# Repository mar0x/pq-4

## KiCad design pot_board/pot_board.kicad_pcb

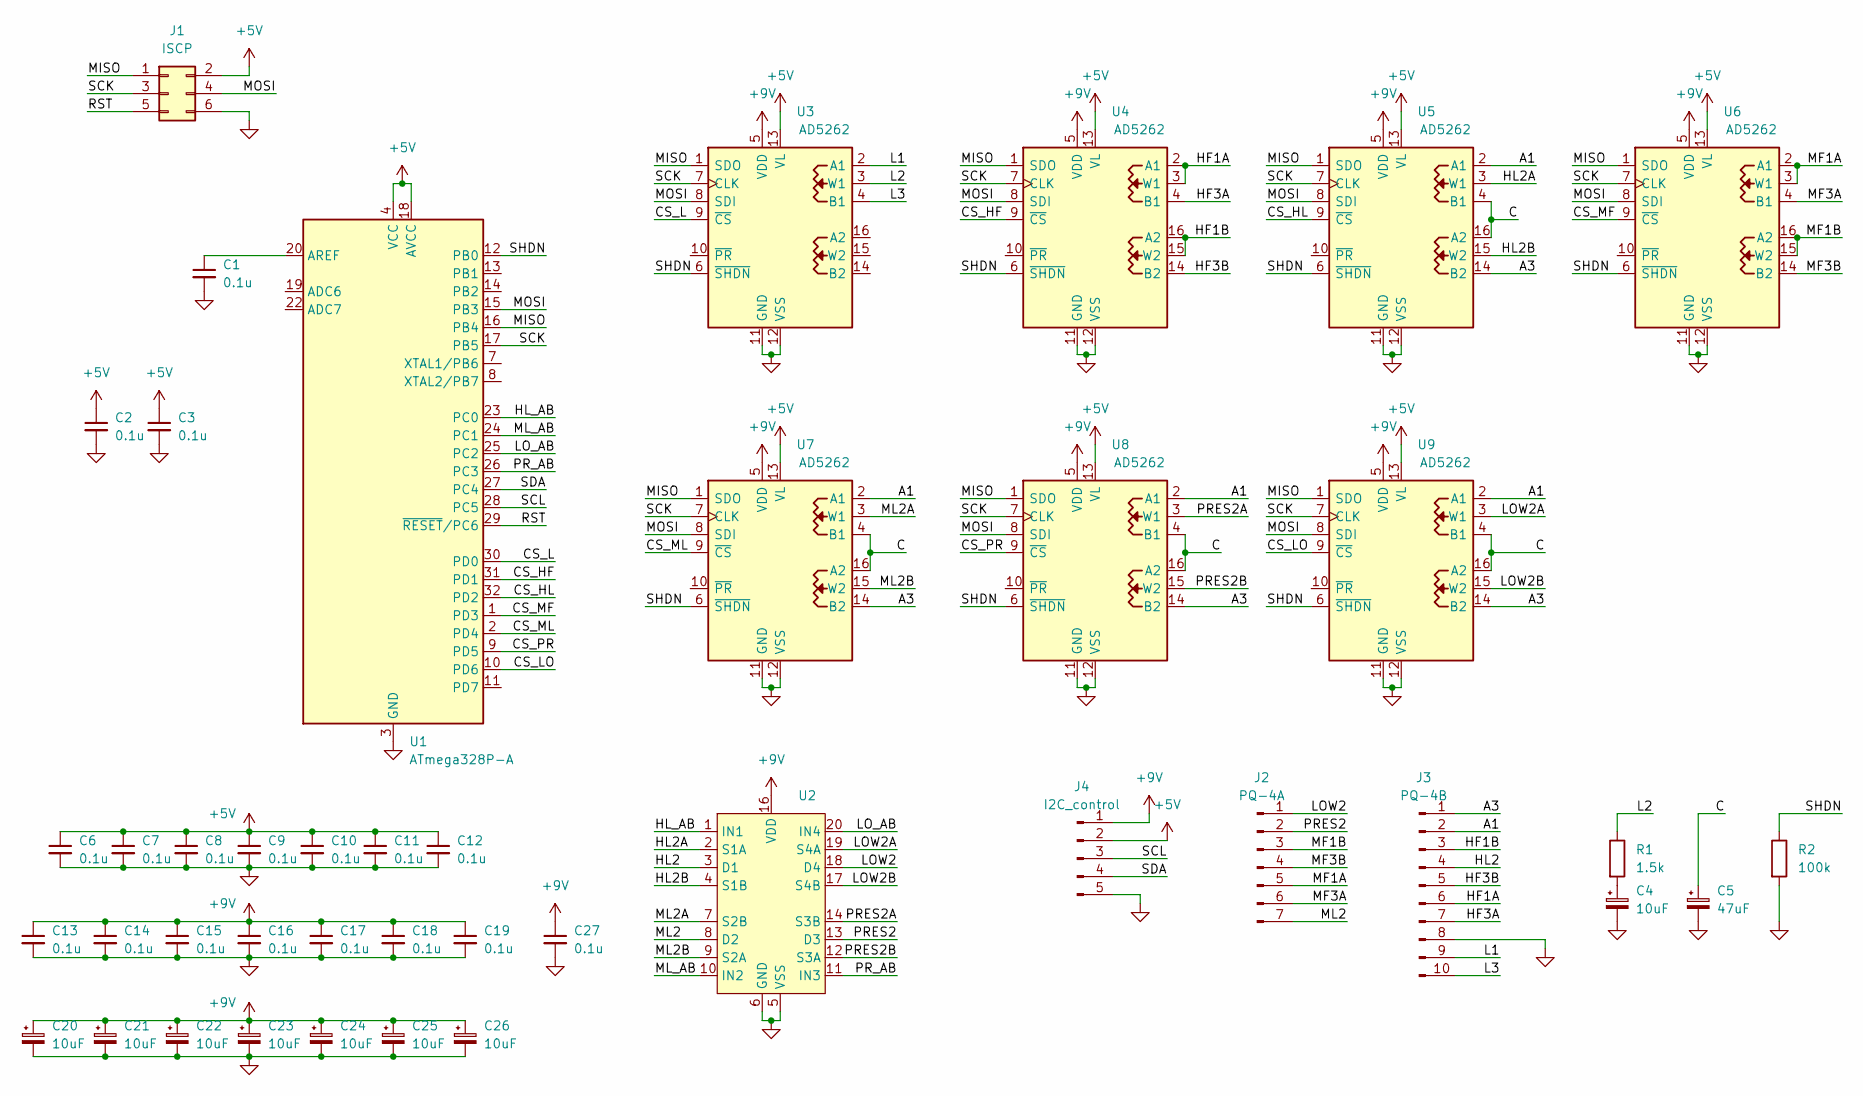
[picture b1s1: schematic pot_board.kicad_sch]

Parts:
C1, C2, C3, C6, C7, C8, C9, C10, C11, C12, C13, C14, C15, C16, C17, C18, C19, C27: 0.1u; C_0805_2012Metric
C4, C20, C21, C22, C23, C24, C25, C26: 10uF; CP_Radial_D4.0mm_P2.00mm
C5: 47uF; CP_Radial_D4.0mm_P2.00mm
J1: ISCP; IDC-Header_2x03_P2.54mm_Vertical
J2: PQ-4A; JST_PH_B7B-PH-K_1x07_P2.00mm_Vertical
J3: PQ-4B; JST_PH_B10B-PH-K_1x10_P2.00mm_Vertical
J4: I2C_control; JST_PH_B5B-PH-K_1x05_P2.00mm_Vertical
R1: 1.5k; R_0805_2012Metric
R2: 100k; R_0805_2012Metric
U1: ATmega328P-A; TQFP-32_7x7mm_P0.8mm
U2: TSSOP-20_4.4x6.5mm_P0.65mm
U3, U4, U5, U6, U7, U8, U9: AD5262; TSSOP-16_4.4x5mm_P0.65mm

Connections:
+5V: C2.1, C3.1, C6.1, C7.1, C8.1, C9.1, C10.1, C11.1, C12.1, J1.2, J4.2, U1.4 (VCC), U1.6 (VCC), U1.18 (AVCC), U3.13 (VL), U4.13 (VL), U5.13 (VL), U6.13 (VL), U7.13 (VL), U8.13 (VL), U9.13 (VL)
+9V: C13.1, C14.1, C15.1, C16.1, C17.1, C18.1, C19.1, C20.1, C21.1, C22.1, C23.1, C24.1, C25.1, C26.1, C27.1, J4.1, U2.16 (VDD), U3.5 (VDD), U4.5 (VDD), U5.5 (VDD), U6.5 (VDD), U7.5 (VDD), U8.5 (VDD), U9.5 (VDD)
/A1: J3.2, U5.2 (A1), U7.2 (A1), U8.2 (A1), U9.2 (A1)
/A3: J3.1, U5.14 (B2), U7.14 (B2), U8.14 (B2), U9.14 (B2)
/C: C5.1, U5.4 (B1), U5.16 (A2), U7.4 (B1), U7.16 (A2), U8.4 (B1), U8.16 (A2), U9.4 (B1), U9.16 (A2)
/CS_HF: U1.31 (PD1), U4.9 (~CS)
/CS_HL: U1.32 (PD2), U5.9 (~CS)
/CS_L: U1.30 (PD0), U3.9 (~CS)
/CS_LO: U1.10 (PD6), U9.9 (~CS)
/CS_MF: U1.1 (PD3), U6.9 (~CS)
/CS_ML: U1.2 (PD4), U7.9 (~CS)
/CS_PR: U1.9 (PD5), U8.9 (~CS)
/HF1A: J3.6, U4.2 (A1), U4.3 (W1)
/HF1B: J3.3, U4.15 (W2), U4.16 (A2)
/HF3A: J3.7, U4.4 (B1)
/HF3B: J3.5, U4.14 (B2)
/HL2: J3.4, U2.3 (D1)
/HL2A: U2.2 (S1A), U5.3 (W1)
/HL2B: U2.4 (S1B), U5.15 (W2)
/HL_AB: U1.23 (PC0), U2.1 (IN1)
/L1: J3.9, U3.2 (A1)
/L2: R1.1, U3.3 (W1)
/L3: J3.10, U3.4 (B1)
/LOW2: J2.1, U2.18 (D4)
/LOW2A: U2.19 (S4A), U9.3 (W1)
/LOW2B: U2.17 (S4B), U9.15 (W2)
/LO_AB: U1.25 (PC2), U2.20 (IN4)
/MF1A: J2.5, U6.2 (A1), U6.3 (W1)
/MF1B: J2.3, U6.15 (W2), U6.16 (A2)
/MF3A: J2.6, U6.4 (B1)
/MF3B: J2.4, U6.14 (B2)
/MISO: J1.1, U1.16 (PB4), U3.1 (SDO), U4.1 (SDO), U5.1 (SDO), U6.1 (SDO), U7.1 (SDO), U8.1 (SDO), U9.1 (SDO)
/ML2: J2.7, U2.8 (D2)
/ML2A: U2.7 (S2B), U7.3 (W1)
/ML2B: U2.9 (S2A), U7.15 (W2)
/ML_AB: U1.24 (PC1), U2.10 (IN2)
/MOSI: J1.4, U1.15 (PB3), U3.8 (SDI), U4.8 (SDI), U5.8 (SDI), U6.8 (SDI), U7.8 (SDI), U8.8 (SDI), U9.8 (SDI)
/PRES2: J2.2, U2.13 (D3)
/PRES2A: U2.14 (S3B), U8.3 (W1)
/PRES2B: U2.12 (S3A), U8.15 (W2)
/PR_AB: U1.26 (PC3), U2.11 (IN3)
/RST: J1.5, U1.29 (~RESET/PC6)
/SCK: J1.3, U1.17 (PB5), U3.7 (CLK), U4.7 (CLK), U5.7 (CLK), U6.7 (CLK), U7.7 (CLK), U8.7 (CLK), U9.7 (CLK)
/SCL: J4.3, U1.28 (PC5)
/SDA: J4.4, U1.27 (PC4)
/SHDN: R2.1, U1.12 (PB0), U3.6 (~SHDN), U4.6 (~SHDN), U5.6 (~SHDN), U6.6 (~SHDN), U7.6 (~SHDN), U8.6 (~SHDN), U9.6 (~SHDN)
GND: C1.2, C2.2, C3.2, C4.2, C5.2, C6.2, C7.2, C8.2, C9.2, C10.2, C11.2, C12.2, C13.2, C14.2, C15.2, C16.2, C17.2, C18.2, C19.2, C20.2, C21.2, C22.2, C23.2, C24.2, C25.2, C26.2, C27.2, J1.6, J3.8, J4.5, R2.2, U1.3 (GND), U1.5 (GND), U1.21 (GND), U2.5 (VSS), U2.6 (GND), U3.11 (GND), U3.12 (VSS), U4.11 (GND), U4.12 (VSS), U5.11 (GND), U5.12 (VSS), U6.11 (GND), U6.12 (VSS), U7.11 (GND), U7.12 (VSS), U8.11 (GND), U8.12 (VSS), U9.11 (GND), U9.12 (VSS)
unnamed: C4.1, R1.2
unnamed: C1.1, U1.20 (AREF)

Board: 2 copper layers, 42 parts (2 on the bottom side), 49 nets, no tracks yet.

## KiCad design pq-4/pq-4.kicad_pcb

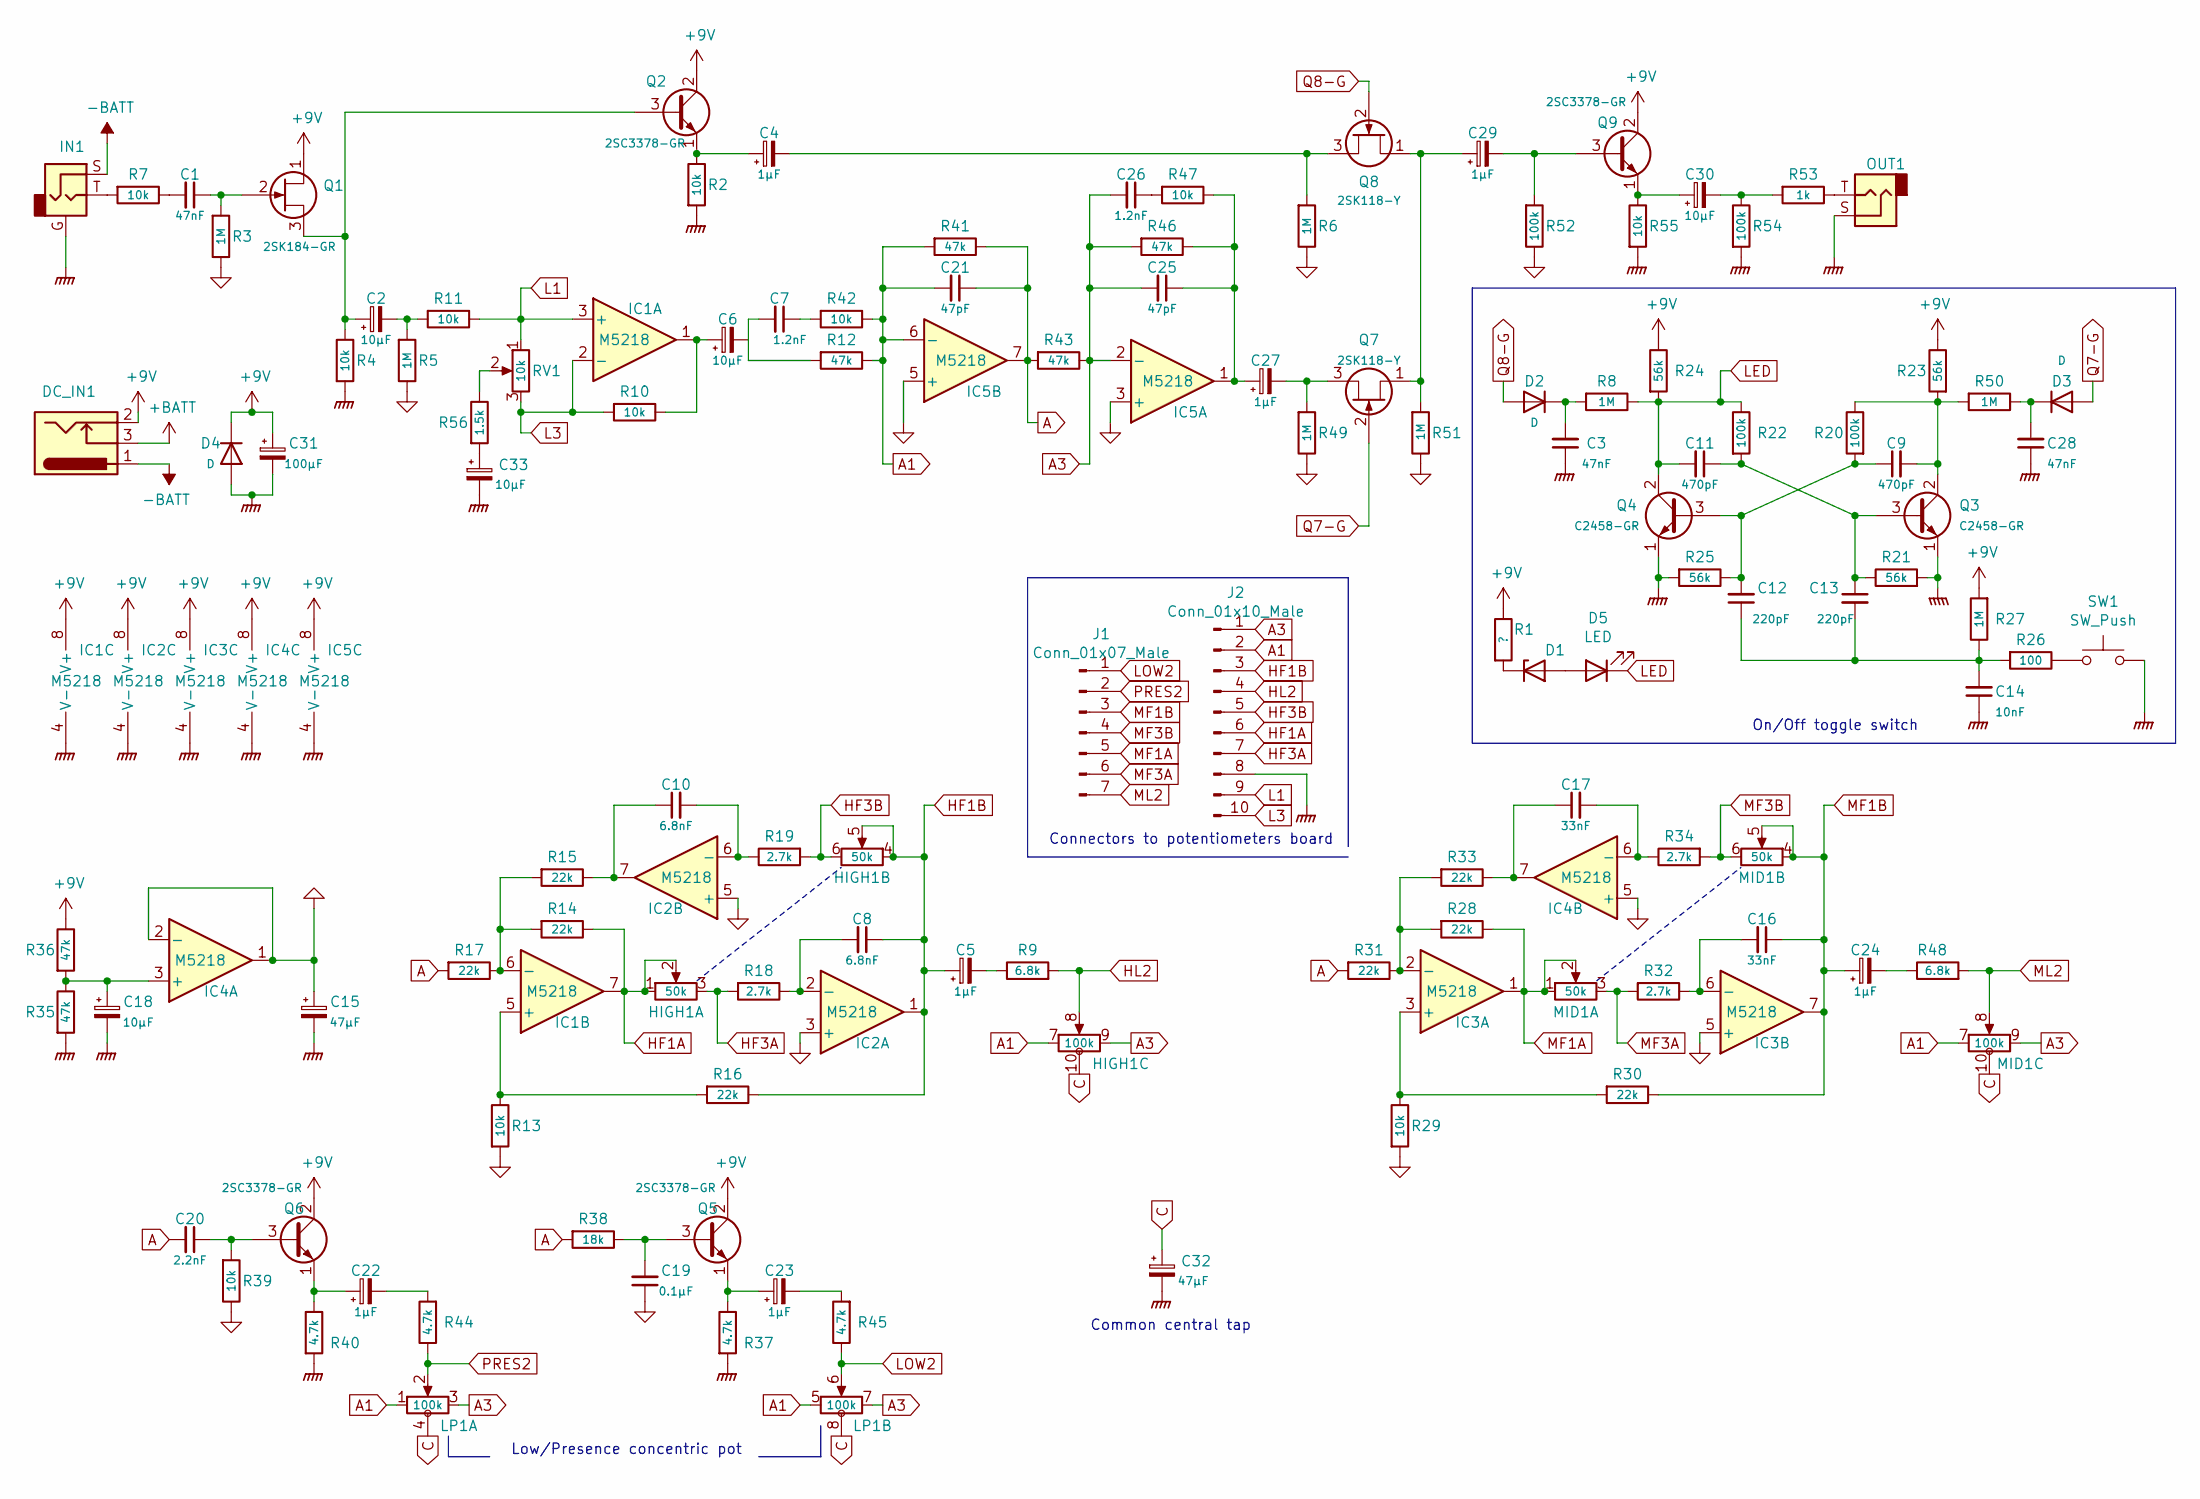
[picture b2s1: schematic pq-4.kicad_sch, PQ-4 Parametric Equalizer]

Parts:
C1, C3, C28: 47nF; C_Rect_L7.0mm_W2.0mm_P5.00mm
C2, C6, C18, C30, C33: 10µF; CP_Radial_D4.0mm_P5.08mm
C4, C5, C22, C23, C24, C27, C29: 1µF; CP_Radial_D4.0mm_P5.08mm
C7, C26: 1.2nF; C_Rect_L7.0mm_W2.0mm_P5.00mm
C8, C10: 6.8nF; C_Rect_L7.0mm_W2.0mm_P5.00mm
C9, C11: 470pF; C_Disc_D5.0mm_W2.5mm_P5.00mm
C12, C13: 220pF; C_Disc_D5.0mm_W2.5mm_P5.00mm
C14: 10nF; C_Rect_L7.0mm_W2.0mm_P5.00mm
C15, C32: 47µF; CP_Radial_D4.0mm_P5.08mm
C16, C17: 33nF; C_Rect_L7.0mm_W2.0mm_P5.00mm
C19: 0.1µF; C_Rect_L7.0mm_W2.0mm_P5.00mm
C20: 2.2nF; C_Rect_L7.0mm_W2.0mm_P5.00mm
C21, C25: 47pF; C_Disc_D5.0mm_W2.5mm_P5.00mm
C31: 100µF; CP_Radial_D4.0mm_P5.08mm
D1: D_Zener_Small; D_T-1_P5.08mm_Horizontal
D2, D3: D; D_T-1_P5.08mm_Horizontal
D4: D; D_5W_P5.08mm_Vertical_KathodeUp
D5: LED
DC_IN1: Barrel_Jack_Switch; BarrelJack_CUI_PJ-102AH_Horizontal
HIGH1: 50k
IC1, IC2, IC3, IC4, IC5: M5218; SIP-8_19x3mm_P2.54mm
IN1: AudioJack2_Ground
J1: Conn_01x07_Male; JST_PH_B7B-PH-K_1x07_P2.00mm_Vertical
J2: Conn_01x10_Male; JST_PH_B10B-PH-K_1x10_P2.00mm_Vertical
LP1: 100k
MID1: 50k
OUT1: AudioJack2
Q1: 2SK184-GR; TO-92S_Wide
Q2, Q5, Q6, Q9: 2SC3378-GR; TO-92S_Wide
Q3, Q4: C2458-GR; TO-92S_Wide
Q7, Q8: 2SK118-Y; TO-92S_Wide
R1: ?; R_Axial_DIN0204_L3.6mm_D1.6mm_P5.08mm_Horizontal
R2, R4, R7, R10, R11, R13, R29, R39, R42, R47, R55: 10k; R_Axial_DIN0204_L3.6mm_D1.6mm_P5.08mm_Horizontal
R3, R5, R6, R8, R27, R49, R50, R51: 1M; R_Axial_DIN0204_L3.6mm_D1.6mm_P5.08mm_Horizontal
R9, R48: 6.8k; R_Axial_DIN0204_L3.6mm_D1.6mm_P5.08mm_Horizontal
R12, R35, R36, R41, R43, R46: 47k; R_Axial_DIN0204_L3.6mm_D1.6mm_P5.08mm_Horizontal
R14, R15, R16, R17, R28, R30, R31, R33: 22k; R_Axial_DIN0204_L3.6mm_D1.6mm_P5.08mm_Horizontal
R18, R19, R32, R34: 2.7k; R_Axial_DIN0204_L3.6mm_D1.6mm_P5.08mm_Horizontal
R20, R22, R52, R54: 100k; R_Axial_DIN0204_L3.6mm_D1.6mm_P5.08mm_Horizontal
R21, R23, R24, R25: 56k; R_Axial_DIN0204_L3.6mm_D1.6mm_P5.08mm_Horizontal
R26: 100; R_Axial_DIN0204_L3.6mm_D1.6mm_P5.08mm_Horizontal
R37, R40, R44, R45: 4.7k; R_Axial_DIN0204_L3.6mm_D1.6mm_P5.08mm_Horizontal
R38: 18k; R_Axial_DIN0204_L3.6mm_D1.6mm_P5.08mm_Horizontal
R53: 1k; R_Axial_DIN0204_L3.6mm_D1.6mm_P5.08mm_Horizontal
R56: 1.5k; R_Axial_DIN0204_L3.6mm_D1.6mm_P5.08mm_Horizontal
RV1: 10k
SW1: SW_Push

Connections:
+9V: C31.1, D4.1 (K), DC_IN1.2, IC1.8 (V+), IC2.8 (V+), IC3.8 (V+), IC4.8 (V+), IC5.8 (V+), Q1.1 (D), Q2.2 (C), Q5.2 (C), Q6.2 (C), Q9.2 (C), R1.1, R23.1, R24.1, R27.2, R36.1
+BATT: DC_IN1.3
-BATT: DC_IN1.1, IN1.S
A: C20.2, C21.1, IC5.7, R17.2, R31.2, R38.2, R41.1, R43.2
A1: C21.2, HIGH1.7, IC5.6 (-), J2.2, LP1.1 (5), LP1.5, MID1.7, R12.1, R41.2, R42.1
A3: C25.2, C26.2, HIGH1.9, IC5.2 (-), J2.1, LP1.3 (7), LP1.7, MID1.9, R43.1, R46.2
C: C32.1, HIGH1.10 (Central_tap), LP1.4 (Central_tap), LP1.8 (Central_tap), MID1.10 (Central_tap)
GNDPWR: C3.1, C14.1, C15.2, C18.2, C28.1, C31.2, C32.2, C33.2, D4.2 (A), IC1.4 (V-), IC2.4 (V-), IC3.4 (V-), IC4.4 (V-), IC5.4 (V-), IN1.G, J2.8, OUT1.S, Q3.1 (E), Q4.1 (E), R2.2, R4.2, R21.2, R25.2, R35.2, R37.2, R40.2, R54.2, R55.2, SW1.2
HF1A: HIGH1.1 (5), HIGH1.2 (6), IC1.7, J2.6, R14.1
HF1B: C5.1, C8.1, HIGH1.4, HIGH1.5, IC2.1, J2.3, R16.1
HF3A: HIGH1.3 (7), J2.7, R18.2
HF3B: HIGH1.6, J2.5, R19.2
HL2: HIGH1.8, J2.4, R9.2
L1: IC1.3 (+), J2.9, R11.1, RV1.1
L3: IC1.2 (-), J2.10, R10.2, RV1.3
LED: C11.2, D5.1 (K), Q4.2 (C), R8.1, R22.1, R24.2
LOW2: J1.1, LP1.6, R45.1
MF1A: IC3.1, J1.5, MID1.1 (5), MID1.2 (6), R28.1
MF1B: C16.1, C24.1, IC3.7, J1.3, MID1.4, MID1.5, R30.1
MF3A: J1.6, MID1.3 (7), R32.2
MF3B: J1.4, MID1.6, R34.2
ML2: J1.7, MID1.8, R48.2
unnamed: C1.1, Q1.2 (G), R3.2
unnamed: C1.2, R7.1
unnamed: C2.1, Q1.3 (S), Q2.3 (B), R4.1
unnamed: C2.2, R5.2, R11.2
unnamed: C3.2, D2.1 (K), R8.2
unnamed: C4.1, Q2.1 (E), R2.1
unnamed: C4.2, Q8.3 (S), R6.2
unnamed: C5.2, R9.1
unnamed: C6.1, IC1.1, R10.1
unnamed: C7.1, R42.2
unnamed: C8.2, IC2.2 (-), R18.1
unnamed: C9.2, Q3.2 (C), R20.1, R23.2, R50.2
unnamed: C10.1, IC2.7, R15.1
unnamed: C10.2, IC2.6 (-), R19.1
unnamed: C11.1, C13.1, Q3.3 (B), R21.1, R22.2
unnamed: C12.1, C13.2, C14.2, R26.2, R27.1
unnamed: C9.1, C12.2, Q4.3 (B), R20.2, R25.1
unnamed: C16.2, IC3.6 (-), R32.1
unnamed: C17.1, IC4.7, R33.1
unnamed: C17.2, IC4.6 (-), R34.1
unnamed: C18.1, IC4.3 (+), R35.1, R36.2
unnamed: C19.2, Q5.3 (B), R38.1
unnamed: C20.1, Q6.3 (B), R39.2
unnamed: C22.1, Q6.1 (E), R40.1
unnamed: C22.2, R44.2
unnamed: C23.1, Q5.1 (E), R37.1
unnamed: C23.2, R45.2
unnamed: C24.2, R48.1
unnamed: C25.1, C27.1, IC5.1, R46.1, R47.1
unnamed: C26.1, R47.2
unnamed: C27.2, Q7.3 (S), R49.2
unnamed: C28.2, D3.1 (K), R50.1
unnamed: C29.1, Q7.1 (D), Q8.1 (D), R51.2
unnamed: C29.2, Q9.3 (B), R52.2
unnamed: C30.1, Q9.1 (E), R55.1
unnamed: C30.2, R53.2, R54.1
unnamed: C33.1, R56.2
unnamed: D1.1 (K), R1.2
unnamed: D1.2 (A), D5.2 (A)
unnamed: IC1.5 (+), R13.1, R16.2
unnamed: IC1.6 (-), R14.2, R15.2, R17.1
unnamed: IC3.2 (-), R28.2, R31.1, R33.2
unnamed: IC3.3 (+), R29.1, R30.2
unnamed: IN1.T, R7.2
unnamed: OUT1.T, R53.1
unnamed: R26.1, SW1.1
unnamed: R56.1, RV1.2
PRES2: J1.2, LP1.2 (6), R44.1
Q7-G: D3.2 (A), Q7.2 (G)
Q8-G: D2.2 (A), Q8.2 (G)
VCC: C15.1, C19.1, IC2.3 (+), IC2.5 (+), IC3.5 (+), IC4.1, IC4.2 (-), IC4.5 (+), IC5.3 (+), IC5.5 (+), R3.1, R5.1, R6.1, R13.2, R29.2, R39.1, R49.1, R51.1, R52.1

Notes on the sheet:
Connectors to potentiometers board
Common central tap
On/Off toggle switch
Low/Presence concentric pot

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
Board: 2 copper layers, 110 parts (0 on the bottom side), 66 nets, no tracks yet.

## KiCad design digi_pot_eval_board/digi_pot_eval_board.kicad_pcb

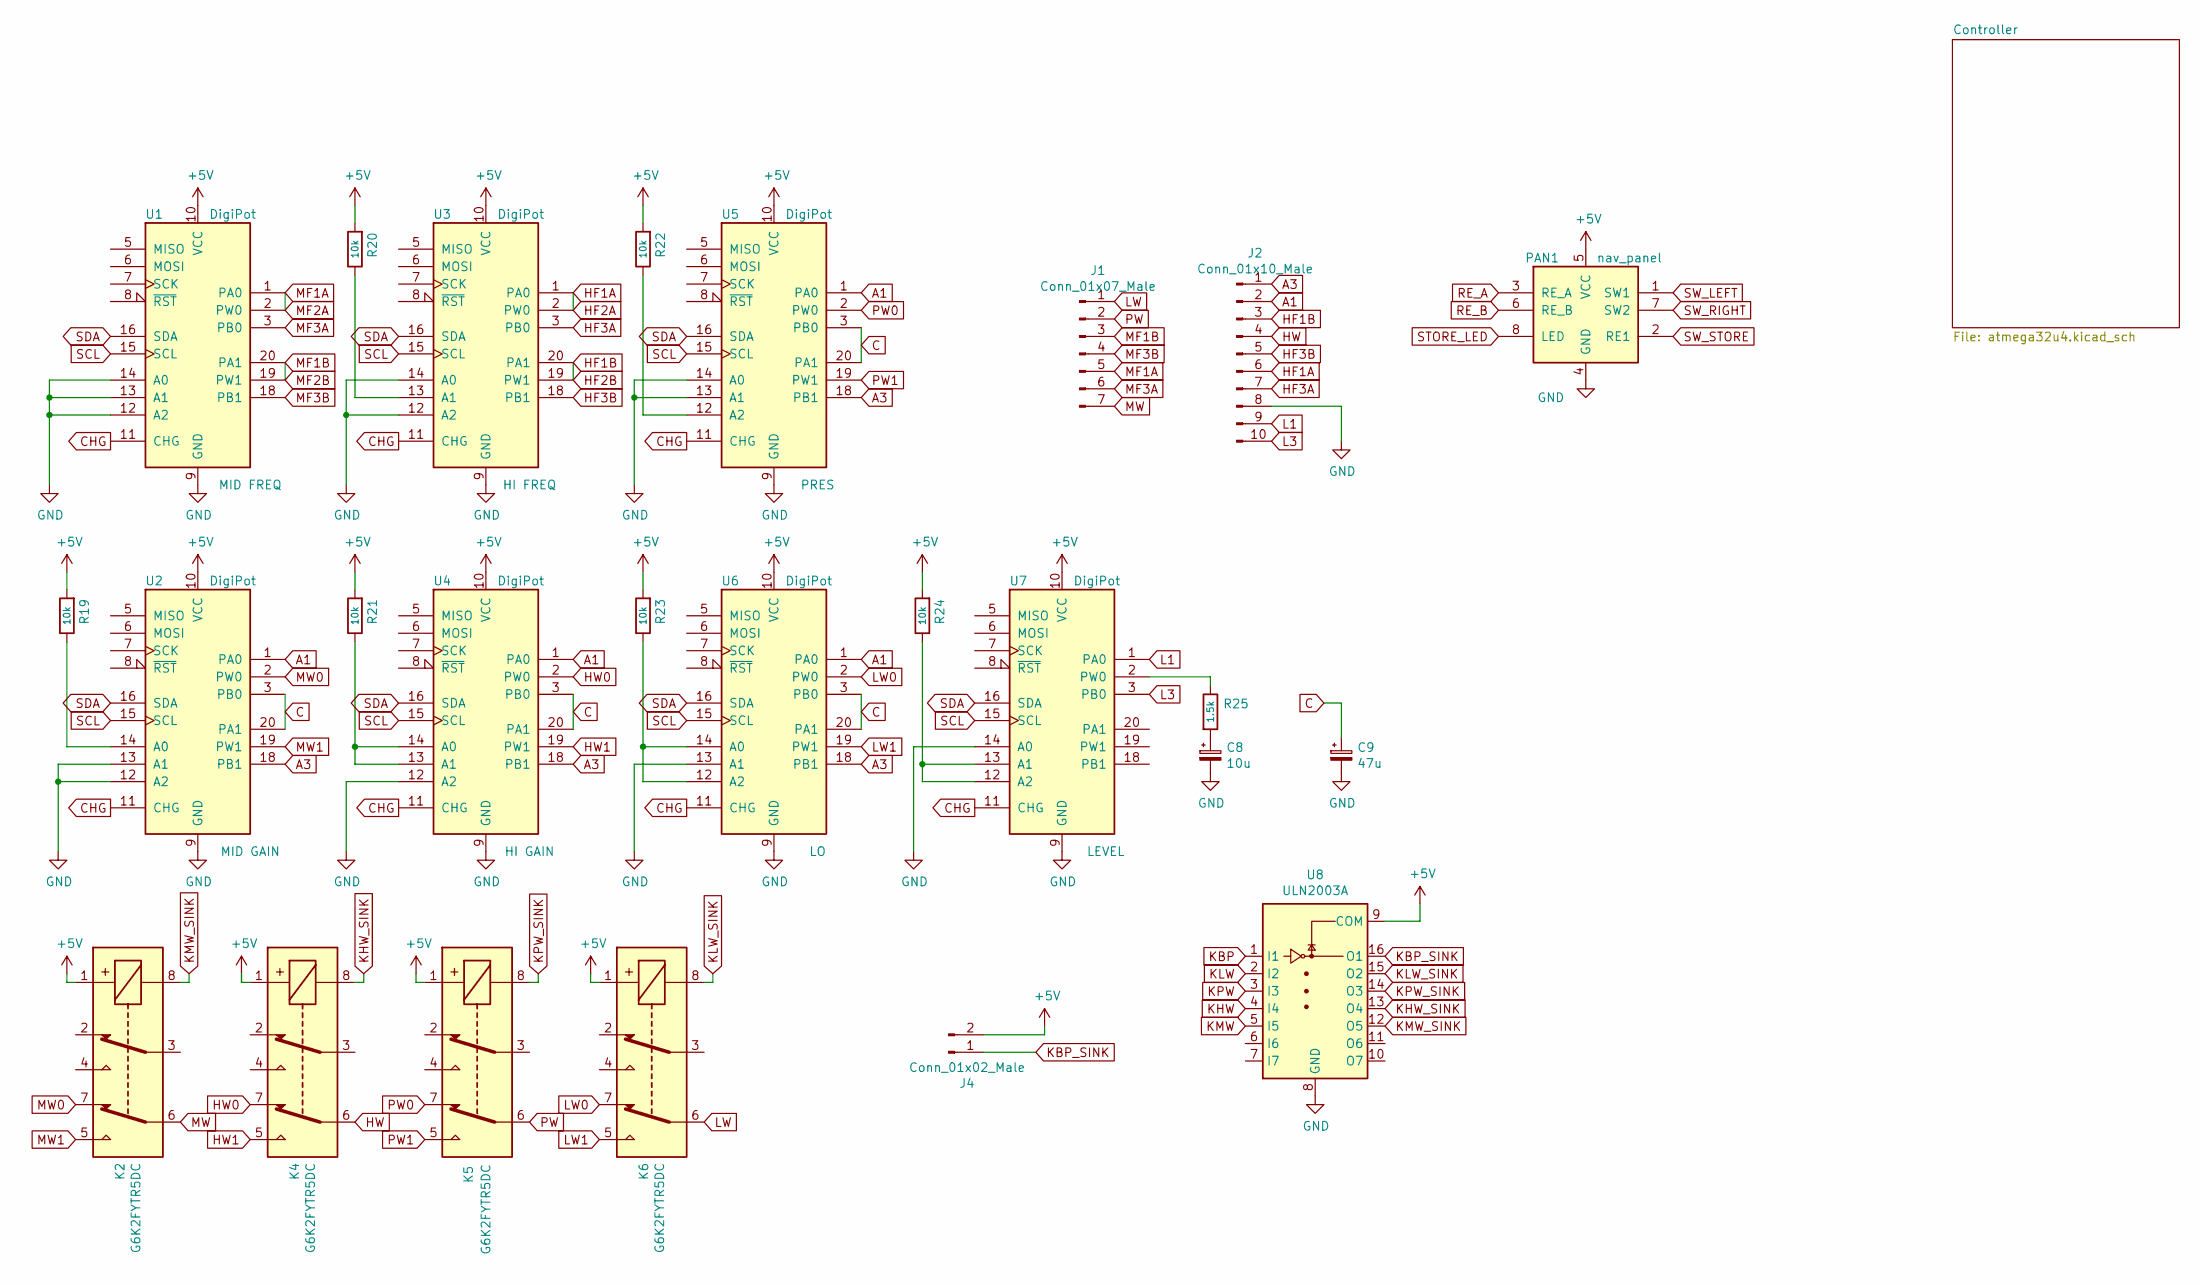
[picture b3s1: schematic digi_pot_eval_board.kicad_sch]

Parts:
C8: 10u; CP_Radial_D4.0mm_P2.00mm
C9: 47u; CP_Radial_D5.0mm_P2.50mm
J1: Conn_01x07_Male; JST_PH_B7B-PH-K_1x07_P2.00mm_Vertical
J2: Conn_01x10_Male; JST_PH_B10B-PH-K_1x10_P2.00mm_Vertical
J4: Conn_01x02_Male; JST_EH_B02B-EH-A_1x02_P2.50mm_Vertical
K2, K4, K5, K6: G6K2FYTR5DC; Relay_DPDT_Omron_G6K-2F-Y
PAN1: nav_panel; nav_panel_SMD
R19, R20, R21, R22, R23, R24: 10k; R_0805_2012Metric_Pad1.15x1.40mm_HandSolder
R25: 1.5k; R_0805_2012Metric_Pad1.15x1.40mm_HandSolder
U1, U2, U3, U4, U5, U6, U7: DigiPot; DigiPot_Vertical_SMD
U8: ULN2003A; SOIC-16_3.9x9.9mm_P1.27mm

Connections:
+5V: J4.2, K2.1, K4.1, K5.1, K6.1, PAN1.5 (VCC), R19.2, R20.2, R21.2, R22.2, R23.2, R24.2, U1.10 (VCC), U2.10 (VCC), U3.10 (VCC), U4.10 (VCC), U5.10 (VCC), U6.10 (VCC), U7.10 (VCC), U8.9 (COM); also elsewhere on the board
A1: J2.2, U2.1 (PA0), U4.1 (PA0), U5.1 (PA0), U6.1 (PA0)
A3: J2.1, U2.18 (PB1), U4.18 (PB1), U5.18 (PB1), U6.18 (PB1)
C: C9.1, U2.3 (PB0), U2.20 (PA1), U4.3 (PB0), U4.20 (PA1), U5.3 (PB0), U5.20 (PA1), U6.3 (PB0), U6.20 (PA1)
CHG: U1.11 (CHG), U2.11 (CHG), U3.11 (CHG), U4.11 (CHG), U5.11 (CHG), U6.11 (CHG), U7.11 (CHG); also elsewhere on the board
GND: C8.2, C9.2, J2.8, PAN1.4 (GND), U1.9 (GND), U1.12 (A2), U1.13 (A1), U1.14 (A0), U2.9 (GND), U2.12 (A2), U2.13 (A1), U3.9 (GND), U3.12 (A2), U3.14 (A0), U4.9 (GND), U4.12 (A2), U5.9 (GND), U5.13 (A1), U5.14 (A0), U6.9 (GND), U6.13 (A1), U7.9 (GND), U7.14 (A0), U8.8 (GND); also elsewhere on the board
HF1A: J2.6, U3.1 (PA0), U3.2 (PW0)
HF1B: J2.3, U3.19 (PW1), U3.20 (PA1)
HF3A: J2.7, U3.3 (PB0)
HF3B: J2.5, U3.18 (PB1)
HW: J2.4, K4.6
HW0: K4.7, U4.2 (PW0)
HW1: K4.5, U4.19 (PW1)
KBP: U8.1 (I1); also elsewhere on the board
KBP_SINK: J4.1, U8.16 (O1)
KHW: U8.4 (I4); also elsewhere on the board
KHW_SINK: K4.8, U8.13 (O4)
KLW: U8.2 (I2); also elsewhere on the board
KLW_SINK: K6.8, U8.15 (O2)
KMW: U8.5 (I5); also elsewhere on the board
KMW_SINK: K2.8, U8.12 (O5)
KPW: U8.3 (I3); also elsewhere on the board
KPW_SINK: K5.8, U8.14 (O3)
L1: J2.9, U7.1 (PA0)
L3: J2.10, U7.3 (PB0)
LW: J1.1, K6.6
LW0: K6.7, U6.2 (PW0)
LW1: K6.5, U6.19 (PW1)
MF1A: J1.5, U1.1 (PA0), U1.2 (PW0)
MF1B: J1.3, U1.19 (PW1), U1.20 (PA1)
MF3A: J1.6, U1.3 (PB0)
MF3B: J1.4, U1.18 (PB1)
MW: J1.7, K2.6
MW0: K2.7, U2.2 (PW0)
MW1: K2.5, U2.19 (PW1)
unnamed: C8.1, R25.2
unnamed: R19.1, U2.14 (A0)
unnamed: R20.1, U3.13 (A1)
unnamed: R21.1, U4.13 (A1), U4.14 (A0)
unnamed: R22.1, U5.12 (A2)
unnamed: R23.1, U6.12 (A2), U6.14 (A0)
unnamed: R24.1, U7.12 (A2), U7.13 (A1)
unnamed: R25.1, U7.2 (PW0)
PW: J1.2, K5.6
PW0: K5.7, U5.2 (PW0)
PW1: K5.5, U5.19 (PW1)
RE_A: PAN1.3 (RE_A); also elsewhere on the board
RE_B: PAN1.6 (RE_B); also elsewhere on the board
SCL: U1.15 (SCL), U2.15 (SCL), U3.15 (SCL), U4.15 (SCL), U5.15 (SCL), U6.15 (SCL), U7.15 (SCL); also elsewhere on the board
SDA: U1.16 (SDA), U2.16 (SDA), U3.16 (SDA), U4.16 (SDA), U5.16 (SDA), U6.16 (SDA), U7.16 (SDA); also elsewhere on the board
STORE_LED: PAN1.8 (LED); also elsewhere on the board
SW_LEFT: PAN1.1 (SW1); also elsewhere on the board
SW_RIGHT: PAN1.7 (SW2); also elsewhere on the board
SW_STORE: PAN1.2 (RE1); also elsewhere on the board

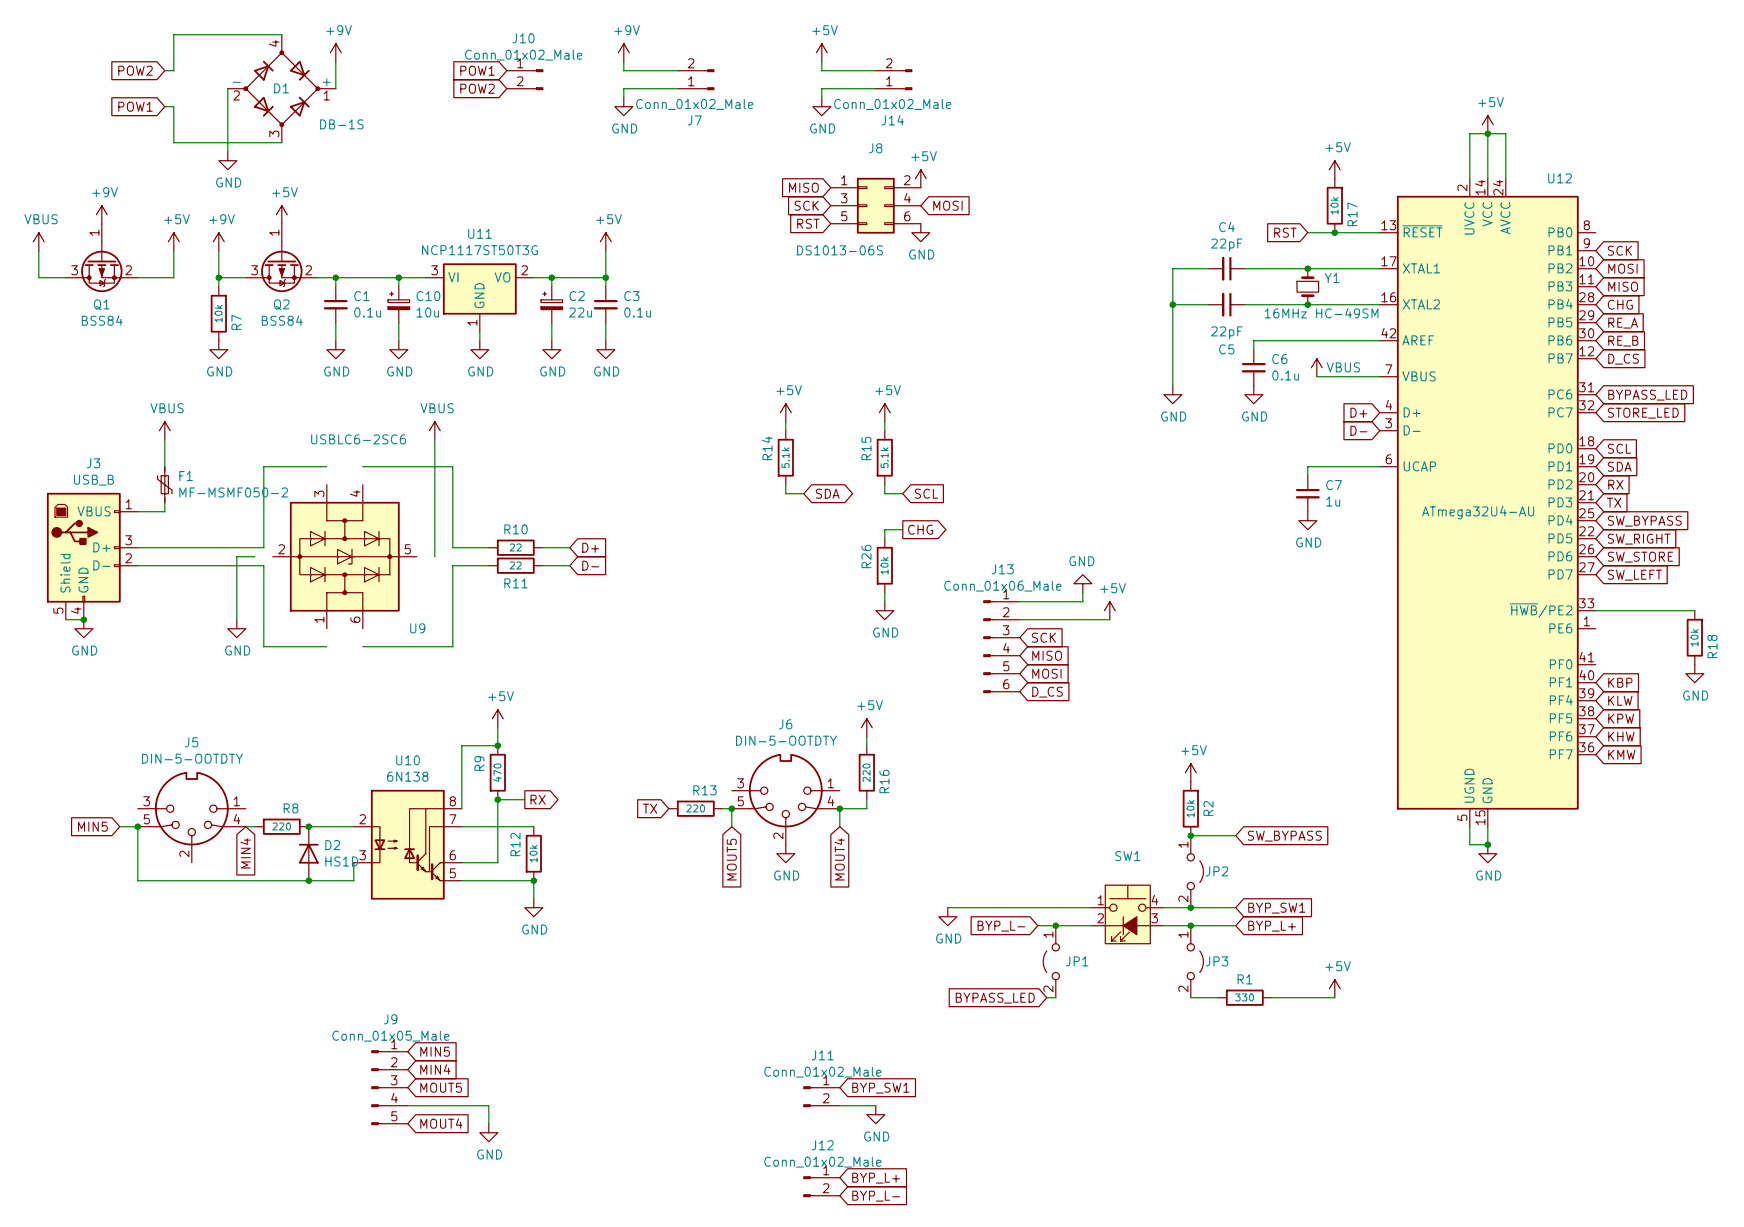
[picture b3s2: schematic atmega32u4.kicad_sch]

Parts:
C1, C3, C6: 0.1u; C_0805_2012Metric_Pad1.15x1.40mm_HandSolder
C2: 22u; CP_EIA-3528-21_Kemet-B_Pad1.50x2.35mm_HandSolder
C4, C5: 22pF; C_0805_2012Metric_Pad1.15x1.40mm_HandSolder
C7: 1u; C_0805_2012Metric_Pad1.15x1.40mm_HandSolder
C10: 10u; CP_EIA-3528-21_Kemet-B_Pad1.50x2.35mm_HandSolder
D1: DB-1S; Diode_Bridge_Vishay_DFS
D2: HS1D; D_SMA
F1: MF-MSMF050-2; Fuse_1812_4532Metric_Pad1.30x3.40mm_HandSolder
J3: USB_B; USB_B_OST_USB-B1HSxx_Horizontal
J5, J6: DIN-5-OOTDTY
J7, J10, J11, J12, J14: Conn_01x02_Male; JST_EH_B02B-EH-A_1x02_P2.50mm_Vertical
J8: DS1013-06S; IDC-Header_2x03_P2.54mm_Vertical
J9: Conn_01x05_Male; JST_EH_B05B-EH-A_1x05_P2.50mm_Vertical
J13: Conn_01x06_Male; JST_EH_B06B-EH-A_1x06_P2.50mm_Vertical
JP1, JP2, JP3: Jumper_NC_Small; PinHeader_1x02_P2.54mm_Vertical
Q1, Q2: BSS84; SOT-23
R1: 330; R_0805_2012Metric_Pad1.15x1.40mm_HandSolder
R2, R7, R12, R17, R18, R26: 10k; R_0805_2012Metric_Pad1.15x1.40mm_HandSolder
R8, R13, R16: 220; R_0805_2012Metric_Pad1.15x1.40mm_HandSolder
R9: 470; R_0805_2012Metric_Pad1.15x1.40mm_HandSolder
R10, R11: 22; R_0805_2012Metric_Pad1.15x1.40mm_HandSolder
R14, R15: 5.1k; R_0805_2012Metric_Pad1.15x1.40mm_HandSolder
SW1: SW_MEC_5G_LED; bypass_panel_THT
U9: USBLC6-2SC6; SOT-23-6
U10: 6N138; DIP-8_W8.89mm_SMDSocket_LongPads
U11: NCP1117ST50T3G; SOT-223-3_TabPin2
U12: ATmega32U4-AU; TQFP-44_10x10mm_P0.8mm
Y1: 16MHz HC-49SM; Crystal_SMD_HC49-SD

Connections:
+5V: C2.1, C3.1, J8.2, J13.2, J14.2, Q1.2 (S), Q2.1 (G), R1.1, R2.2, R9.1, R14.1, R15.1, R16.2, R17.2, U10.8 (VCC), U11.2 (VO), U12.2 (UVCC), U12.14 (VCC), U12.24 (AVCC), U12.34 (VCC), U12.44 (AVCC); also elsewhere on the board
+9V: D1.1 (+), J7.2, Q1.1 (G), Q2.3 (D), R7.2
BYPASS_LED: JP1.2 (B), U12.31 (PC6)
BYP_L+: J12.1, JP3.1 (A), SW1.3 (K)
BYP_L-: J12.2, JP1.1 (A), SW1.2
BYP_SW1: J11.1, JP2.2 (B), SW1.4 (A)
CHG: R26.1, U12.28 (PB4); also elsewhere on the board
D+: R10.1, U12.4 (D+)
D-: R11.1, U12.3 (D-)
D_CS: J13.6, U12.12 (PB7)
GND: C1.2, C2.2, C3.2, C4.2, C5.2, C6.2, C7.2, C10.2, D1.2 (-), J3.4 (GND), J3.5 (Shield), J6.2, J7.1, J8.6, J9.4, J11.2, J13.1, J14.1, R7.1, R12.2, R18.1, R26.2, SW1.1, U9.2 (GND), U10.5 (GND), U11.1 (GND), U12.5 (UGND), U12.15 (GND), U12.23 (GND), U12.35 (GND), U12.43 (GND); also elsewhere on the board
KBP: U12.40 (PF1); also elsewhere on the board
KHW: U12.37 (PF6); also elsewhere on the board
KLW: U12.39 (PF4); also elsewhere on the board
KMW: U12.36 (PF7); also elsewhere on the board
KPW: U12.38 (PF5); also elsewhere on the board
MIN4: J5.4, J9.2, R8.2
MIN5: D2.2 (A), J5.5, J9.1, U10.3 (C2)
MISO: J8.1, J13.4, U12.11 (PB3)
MOSI: J8.4, J13.5, U12.10 (PB2)
MOUT4: J6.4, J9.5, R16.1
MOUT5: J6.5, J9.3, R13.1
unnamed: C1.1, C10.1, Q2.2 (S), U11.3 (VI)
unnamed: C4.1, U12.17 (XTAL1), Y1.1
unnamed: C5.1, U12.16 (XTAL2), Y1.2
unnamed: C6.1, U12.42 (AREF)
unnamed: C7.1, U12.6 (UCAP)
unnamed: D2.1 (K), R8.1, U10.2 (C1)
unnamed: F1.2, J3.1 (VBUS)
unnamed: J3.2 (D-), U9.1 (I/O1)
unnamed: J3.3 (D+), U9.3 (I/O2)
unnamed: JP3.2 (B), R1.2
unnamed: R10.2, U9.4 (I/O2)
unnamed: R11.2, U9.6 (I/O1)
unnamed: R12.1, U10.7 (VO1)
unnamed: R18.2, U12.33 (~HWB/PE2)
POW1: D1.3, J10.1
POW2: D1.4, J10.2
RE_A: U12.29 (PB5); also elsewhere on the board
RE_B: U12.30 (PB6); also elsewhere on the board
RST: J8.5, R17.1, U12.13 (~RESET)
RX: R9.2, U10.6 (VO2), U12.20 (PD2)
SCK: J8.3, J13.3, U12.9 (PB1)
SCL: R15.2, U12.18 (PD0); also elsewhere on the board
SDA: R14.2, U12.19 (PD1); also elsewhere on the board
STORE_LED: U12.32 (PC7); also elsewhere on the board
SW_BYPASS: JP2.1 (A), R2.1, U12.25 (PD4)
SW_LEFT: U12.27 (PD7); also elsewhere on the board
SW_RIGHT: U12.22 (PD5); also elsewhere on the board
SW_STORE: U12.26 (PD6); also elsewhere on the board
TX: R13.2, U12.21 (PD3)
VBUS: F1.1, Q1.3 (D), U9.5 (VBUS), U12.7 (VBUS)

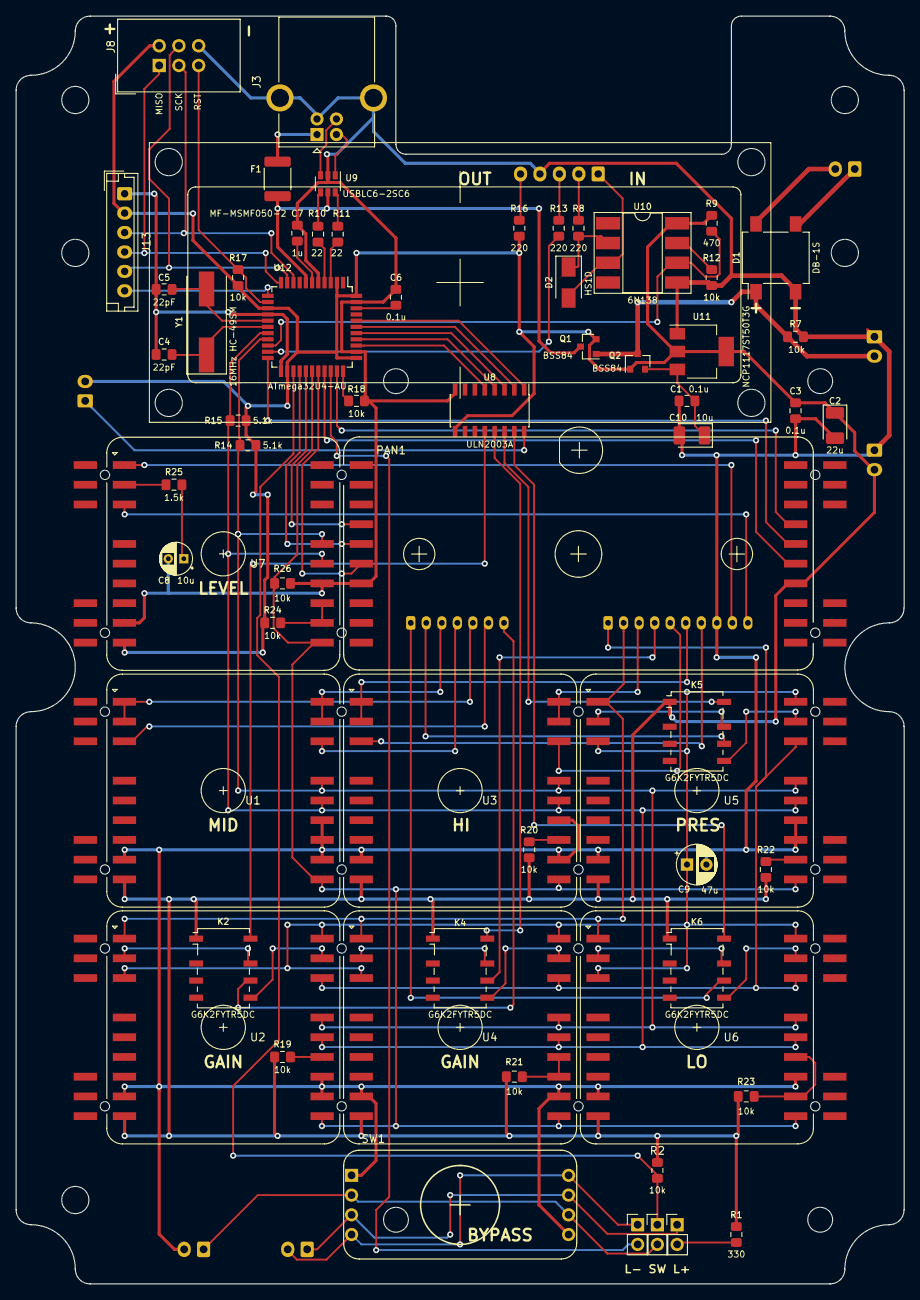
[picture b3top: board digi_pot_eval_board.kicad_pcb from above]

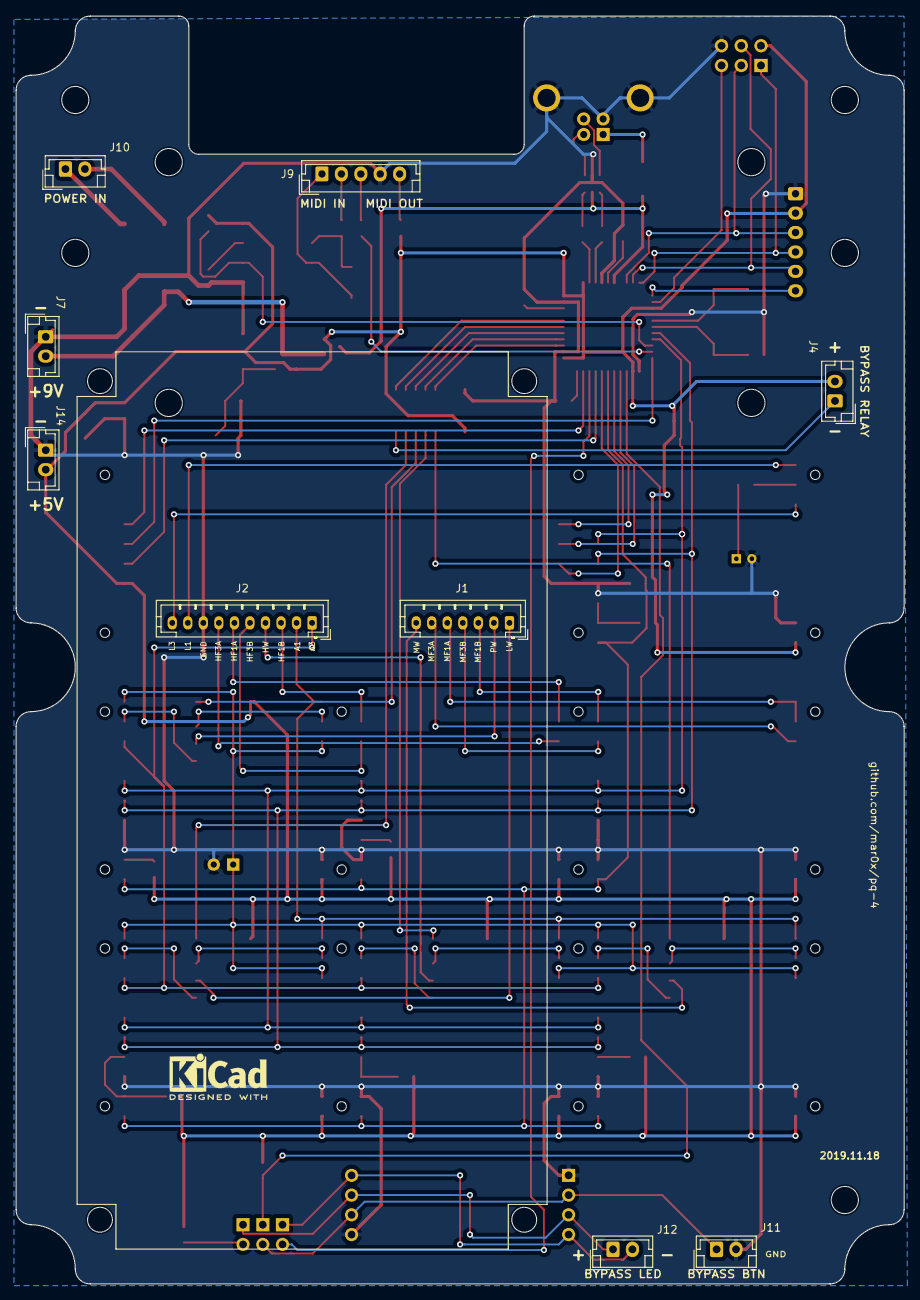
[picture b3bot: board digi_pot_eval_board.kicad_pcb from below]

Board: 2 copper layers, 114.3 x 163.2 mm, 71 parts (9 on the bottom side), 90 nets.
